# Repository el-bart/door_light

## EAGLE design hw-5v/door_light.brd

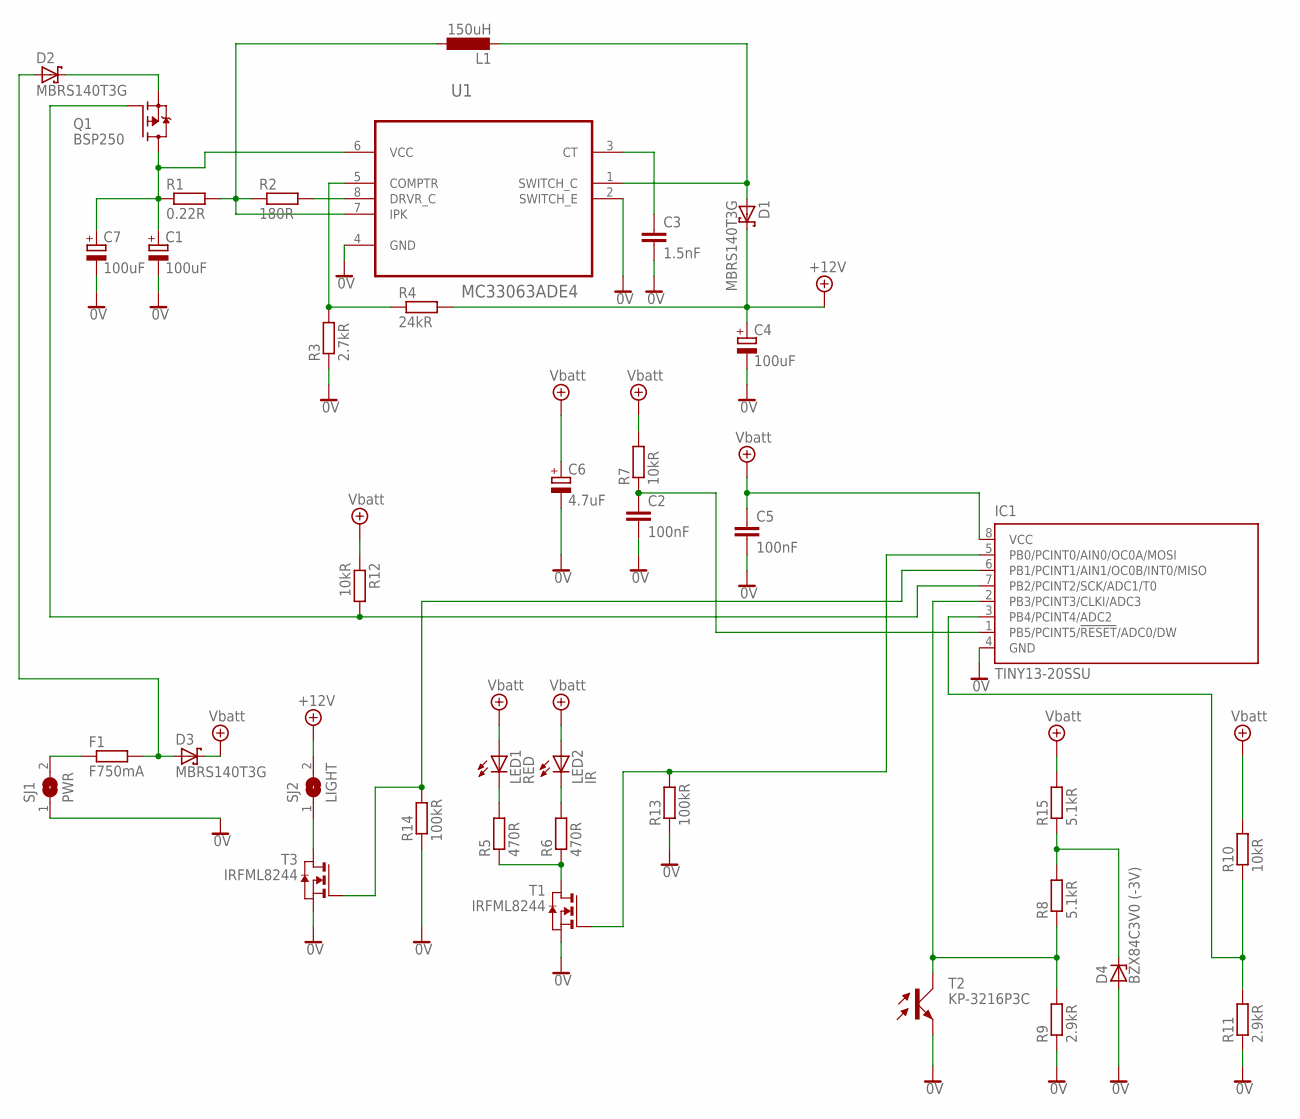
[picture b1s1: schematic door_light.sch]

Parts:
C1, C4, C7: 100uF; 153CLV-0810
C2, C5: 100nF; C1206
C3: 1.5nF; C1206
C6: 4.7uF; 153CLV-0405
D1, D2, D3: MBRS140T3G; SMB
D4: BZX84C3V0 (-3V); TO236
F1: F750mA; MINI_MELF-0207W
IC1: TINY13-20SSU; 8S1
L1: 150uH; PIS2816
LED1: RED; CHIPLED_0603
LED2: IR; CHIPLED_1206
Q1: BSP250; SOT223
R1: 0.22R; M1206
R2: 180R; R0603
R3: 2.7kR; R0603
R4: 24kR; R0603
R5, R6: 470R; R0603
R7, R10, R12: 10kR; R0603
R8, R15: 5.1kR; R0603
R9, R11: 2.9kR; R0603
R13, R14: 100kR; R0603
SJ1: PWR; SJW
SJ2: LIGHT; SJW
T1, T3: IRFML8244; SOT-23
T2: KP-3216P3C; OPTO-TRANS-SIEMENS_BP103
U1: MC33063ADE4; SOIC127P600X175-8N

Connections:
0V: C1.-, C2.2, C3.2, C4.-, C5.2, C6.-, C7.-, D4.A, IC1.4 (GND), R3.1, R9.1, R11.1, R13.1, R14.1, SJ1.1, T1.2 (S), T2.EMITER (E), T3.2 (S), U1.2 (SWITCH_E), U1.4 (GND)
+4.1V: C5.1, C6.+, D3.C, IC1.8 (VCC), LED1.A, LED2.A, R7.2, R10.2, R12.1, R15.2
+12V: C4.+, D1.C, R4.2, SJ2.2
unnamed: LED1.C, R5.2
unnamed: LED2.C, R6.2
unnamed: C1.+, C7.+, Q1.2 (D), Q1.4 (D), R1.1, U1.6 (VCC)
unnamed: R5.1, R6.1, T1.1 (D)
unnamed: D2.C, Q1.3 (S)
unnamed: D4.C, R8.2, R15.1
unnamed: SJ2.1, T3.1 (D)
unnamed: F1.1, SJ1.2
unnamed: C2.1, IC1.1 (PB5/PCINT5/!RESET!/ADC0/DW), R7.1
unnamed: C3.1, U1.3 (CT)
unnamed: D1.A, L1.2, U1.1 (SWITCH_C)
unnamed: IC1.2 (PB3/PCINT3/CLKI/ADC3), R8.1, R9.2, T2.COLLECTOR (C)
unnamed: IC1.7 (PB2/PCINT2/SCK/ADC1/T0), Q1.1 (G), R12.2
unnamed: IC1.5 (PB0/PCINT0/AIN0/OC0A/MOSI), R13.2, T1.3 (G)
unnamed: R2.2, U1.8 (DRVR_C)
unnamed: L1.1, R1.2, R2.1, U1.7 (IPK)
unnamed: IC1.3 (PB4/PCINT4/ADC2), R10.1, R11.2
unnamed: R3.2, R4.1, U1.5 (COMPTR)
unnamed: IC1.6 (PB1/PCINT1/AIN1/OC0B/INT0/MISO), R14.2, T3.3 (G)
unnamed: D2.A, D3.A, F1.2

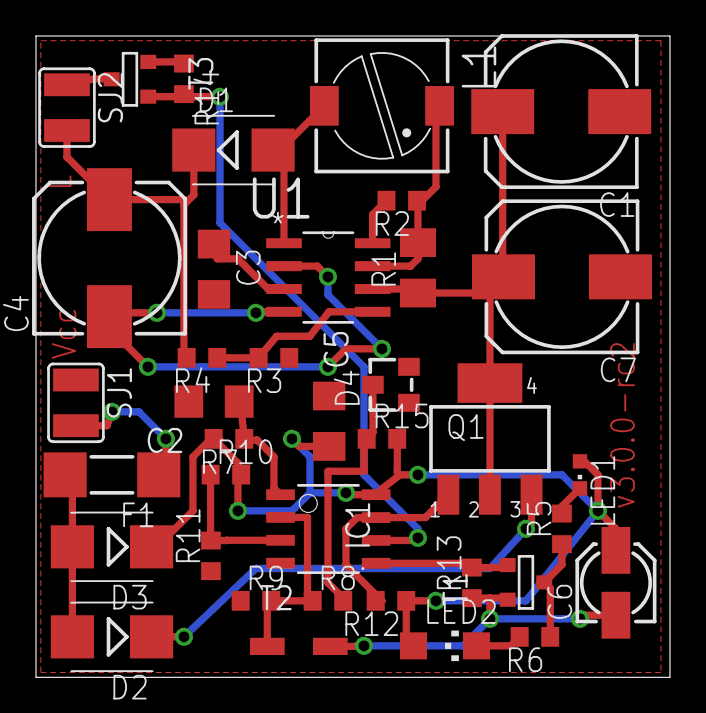
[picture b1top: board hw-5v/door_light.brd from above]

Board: 2 copper layers, 35.2 x 35.6 mm, 38 parts (0 on the bottom side), 23 nets.

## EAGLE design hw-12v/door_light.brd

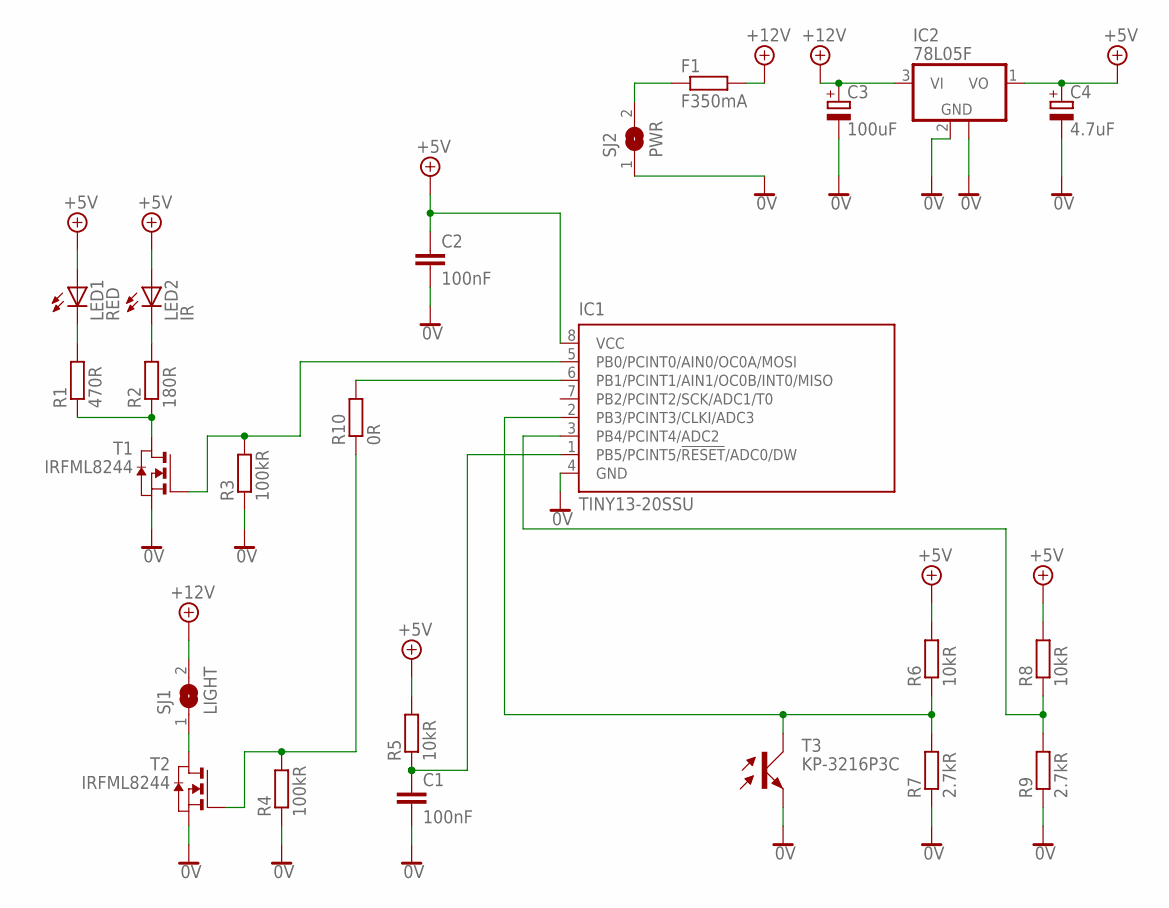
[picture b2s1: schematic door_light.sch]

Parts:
C1, C2: 100nF; C1206
C3: 100uF; 153CLV-0810
C4: 4.7uF; 153CLV-0405
F1: F350mA; MINI_MELF-0204W
IC1: TINY13-20SSU; 8S1
IC2: 78L05F; SOT89
LED1: RED; CHIPLED_0603
LED2: IR; CHIPLED_1206
R1: 470R; R0603
R2: 180R; R0603
R3, R4: 100kR; R0603
R5, R6, R8: 10kR; R0603
R7, R9: 2.7kR; R0603
R10: 0R; R1206W
SJ1: LIGHT; SJW
SJ2: PWR; SJW
T1, T2: IRFML8244; SOT-23
T3: KP-3216P3C; OPTO-TRANS-SIEMENS_BP103

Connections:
0V: C1.2, C2.2, C3.-, C4.-, IC1.4 (GND), IC2.2 (GND), IC2.2@1 (GND), R3.1, R4.1, R7.1, R9.1, SJ2.1, T1.2 (S), T2.2 (S), T3.EMITER (E)
+5V: C2.1, C4.+, IC1.8 (VCC), IC2.1 (VO), LED1.A, LED2.A, R5.2, R6.2, R8.2
+12V: C3.+, F1.2, IC2.3 (VI), SJ1.2
unnamed: LED1.C, R1.2
unnamed: LED2.C, R2.2
unnamed: SJ1.1, T2.1 (D)
unnamed: R1.1, R2.1, T1.1 (D)
unnamed: R4.2, R10.1, T2.3 (G)
unnamed: F1.1, SJ2.2
unnamed: C1.1, IC1.1 (PB5/PCINT5/!RESET!/ADC0/DW), R5.1
unnamed: IC1.2 (PB3/PCINT3/CLKI/ADC3), R6.1, R7.2, T3.COLLECTOR (C)
unnamed: IC1.6 (PB1/PCINT1/AIN1/OC0B/INT0/MISO), R10.2
unnamed: IC1.5 (PB0/PCINT0/AIN0/OC0A/MOSI), R3.2, T1.3 (G)
unnamed: IC1.3 (PB4/PCINT4/ADC2), R8.1, R9.2

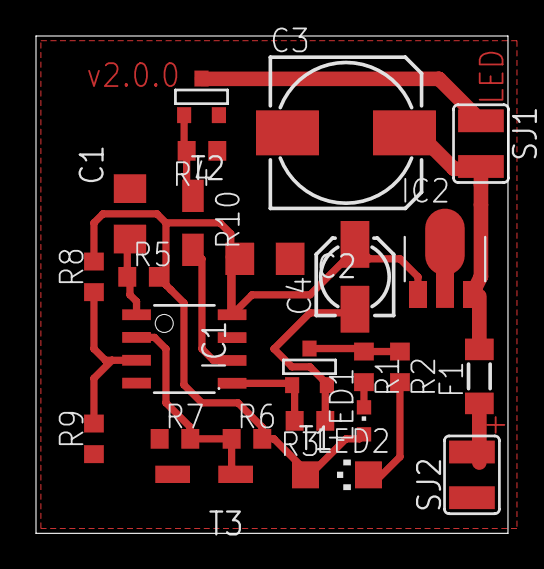
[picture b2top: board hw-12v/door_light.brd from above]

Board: 2 copper layers, 26.2 x 27.6 mm, 24 parts (0 on the bottom side), 14 nets.

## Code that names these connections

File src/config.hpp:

/*
 * config.hpp
 *
 */
#ifndef INCLUDE_CONFIG_HPP_FILE
#define INCLUDE_CONFIG_HPP_FILE

#include <inttypes.h>
#include <avr/io.h>

//
// basic constants
//

// units commonly used
constexpr uint32_t kHz=1000L;
constexpr uint32_t MHz=1000L*kHz;

// clock frequency (9.6MHz with preskaler set to 8)
constexpr uint32_t fcpu = (9*MHz+600*kHz)/8;
// needs to be a define as well...
#define F_CPU fcpu

//
// common types
//
using Millivolts = uint16_t;

//
// misc settings
//

// bits on port definitions
namespace Pin
{
constexpr auto ctrlLed = _BV(PB0);  // control and IR LEDs
constexpr auto light   = _BV(PB1);  // main light
constexpr auto dcDc    = _BV(PB2);  // main light power supply (DC/DC)
constexpr auto irIn    = _BV(PB3);  // IR phototransistor voltage monitoring input
constexpr auto vccIn   = _BV(PB4);  // supply voltage monitoring input
}

// light-related settings
namespace Light
{
constexpr uint8_t irSamples  = 18;      // number of samples to collect per second (each sample is an average of measurements in a corresponding period).
                                        // keep this value, so that PWM's frequency divided by this gives a power of 2 - otherwise code will become big...
constexpr uint8_t irFill     = 50;      // fill level of the PWM for Ctrl setting; 0-255

constexpr uint8_t lightFill  = 0x00;    // PWM fill for main light DC/DC: 0-255

constexpr uint8_t dimIn      =  1;      // number of seconds dim-in should last
constexpr uint8_t lightOn    = 35;      // number of seconds light should remain fully on
constexpr uint8_t dimOut     =  6;      // number of seconds dim-out should last

constexpr uint8_t graceOn    = dimIn+2; // ammount of time where reseting is not possible (avoids blinking)
}

// basic thresholds
namespace Voltage
{
constexpr uint8_t    maxVccThresholdBreach =    3;  // maxumu number of times minimal Vcc threshold can be breached before going down.
constexpr Millivolts minVcc                = 3300;  // minimum operational voltage (3.3[V]);
constexpr Millivolts irThreshold           =   30;  // voltage difference to treat as a trigger (in millivolts)
}

#endif

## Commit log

2013-02-19 datasheets for the components used
2013-02-19 added hardware board
2013-02-21 added version number on board
2013-02-21 added 3rd version number on board
2013-02-22 board overlay limited to actual board's size; minor elements' labels re-ordering
2013-02-26 manual test: application to blink white ledas and control leds
2013-02-26 added compiled elements to the ignore list
2013-02-28 test app to turn everything off
2013-02-28 makefile now is generic
2013-02-28 generic makefile is now used for mtests
2013-02-28 added main build tree
2013-02-28 fuses fixed...
2013-02-28 new build v2.3.1 with protection agains accidental fuses overwrite
2013-02-28 pinout map
2013-02-28 RC frequency is 9.6/8==1.2MHz
2013-02-28 marked ADC number of phototransistor pin
2013-02-28 draft that enables to turn on/off light by approaching hand
2013-02-28 working version (simple though)
2013-02-28 minor cleanup
2013-03-05 TODOs added
2013-06-27 int_t0 test
2013-06-27 ignore files list
2013-06-27 removed leftover from bzr
2013-08-23 TODO on USB added
2013-09-26 TODO moved to devtodo
2013-09-26 more TODOs
2013-11-08 TODO added - new idea on how to make the board
2013-11-09 new idea in english ;)
2013-11-09 documentation update - now PCB is SMD
2013-11-09 TODOs updated
2013-11-09 activeated more layers on pcb view
2013-11-09 pinout updated
2013-11-10 TODO added
2013-11-10 fixed resistor voltage divider
2013-11-10 pads for power and LED connecting are now SMD as well
2013-11-12 coil type changed (bigger one)
2013-11-12 minor alignment update on PCB
2013-11-12 rc-number changed on PCB (not yet labeled though)
2013-11-14 fixed IR led size (was 805, should be 1206)
2013-11-14 replaced fuse with the one of a proper type and size (1812)
2013-11-14 fixed labels on PCB
2013-11-14 blink code update to blink all ports at once (for now)
2013-11-14 infrared elements datasheets added
2013-11-14 fixed invalid path under LED1
2013-11-14 180R size changed from 1206 to 603
2013-11-14 DC/DC converter is nowe powered...
2013-11-14 added missing R to GND from transistors' gates
2013-11-14 minor fixes and first poritng steps forward new software version
2013-11-14 added vim temp failed to ignore list
2013-11-15 Adc moved to separate file + code updated to use new setup
2013-11-15 added dropping 2 least signifficant bits from ADC as a noise
2013-11-15 example application blinking in a way reflecting voltage change
2013-11-15 readme added to state that device needs to be programmed in a slow mode
2013-11-15 removed unused header
2013-11-15 Leds now have separate control classes
2013-11-15 more constants added
2013-11-15 updated 'off' application to new board
2013-11-15 Sampler - class keeping multiple samples of data in a circular buffer
2013-11-15 added power saving mode class
2013-11-15 Pwm is a work in progress
2013-11-15 PWM integration to main has started
2013-11-15 ligh controlling classes are to be reworked
2013-11-15 adding enable/disable and fill() to PWM usage (Led*) - work in progress
2013-11-15 fixed values being set
2013-11-15 default fill for ctrl leds is now in config
2013-11-15 fixed PWM to work as expected, when connected to p-mosfet on output
2013-11-15 removed some garbage from main()
2013-11-15 added method for obtaining PWM's frequency (at compile time)
2013-11-15 replaced on-bard big fuse with the smaller one (the one that has been actually bought)
2013-11-15 Millivolts is now global typedef; draft for the low power handling facility
2013-11-18 created config/Light namespace for light-related settings
2013-11-18 light fill moved to a config
2013-11-18 low power handle has been implemented and is checked once a second
2013-11-18 light triggering work in progress
2013-11-18 added TODOs for 5v version of the hardware
2013-11-18 more TODOs for 12v schematic
2013-11-18 fixed few not-so-bright-namings on the schemas
2013-11-18 added n-mosfet datasheet
2013-11-18 some note on IR elements (after doing measurements)
2013-11-18 IR LED's current note
2013-11-18 added more verbose datasheet on IR diode
2013-11-18 temporary commit
2013-11-18 reverting last commit on main.cpp
2013-11-18 new 12V schema
2013-11-18 added renumerate temp file to git ignores
2013-11-18 recalculated some resitors values
2013-11-19 elements are now more compact
2013-11-19 fixed coliding Vcc and GND on board layout
2013-11-19 fixed R5 size (was 40x should be 603)
2013-11-19 fuse changed from 750mA to 350mA
2013-11-20 TODO added on hardware
2013-11-20 PWM::frequency() now returns more accurate value
2013-11-20 Sampler::average() added
2013-11-20 fixed ADC disabing; removed dropping 2lsbs of ADC result as a noise - nosise is being averaged elsewhere
2013-11-20 working version of light on/off, w/o dim-in/out
2013-11-20 fixed PWM for channel B which is now n-mosfet as well (inverted polarity is NOT required)
2013-11-20 fixed light led control + both led derive privately from implementation
2013-11-20 Sampler has now fill() and size() methods
2013-11-20 main now works fine with real power leds turned on as well
2013-11-20 dim handler draft
2013-11-20 dimming works fine - needs to be integrated with IR readings though
2013-11-20 working version w/o Sampler - just simple 'prev' value, updated during start() and once a second
2013-11-20 minimum Vcc is now 3.3[V] (3x1.1 == 3x low-power eneloops)
2013-11-20 low power handler has been reworked to have check and halt() calls separate, to allow user's code to be added, before halting
2013-11-20 added low power handing code to main()
2013-11-20 minor style and comment fixed + constants improvements
2013-11-20 class for watchdog handling
2013-11-20 watchdog added to main code
2013-11-20 most TODOs marked as done (or removed)
2013-11-20 TODO added on fluorecesnce light
2013-11-20 fixed issue with fluoroluminescence light by adding average values of measurements
2013-11-20 changed board name to v2.0.0 on 12V version
2013-12-04 added DC/DC on/off support in software
2013-12-04 12V version schema is ready, TODOs fixed; PCB is draft-done - to be tested and improved
2013-12-05 route fixes; changed fuse to bigger package (1A)
2013-12-09 added FIR filter model (octave file)
2013-12-09 temporary octave files are added to ignore list
2013-12-12 fixed invalid 10kR resistor size
2013-12-12 fixed invalid p-mosfet control
2013-12-12 comments fixes; added constant for grace on-time
2013-12-12 added todo o missing resistor
2013-12-12 grace period when starting added
2013-12-12 size of the binary decreased thanks to dividing by the power of 2
2013-12-12 comment on irSamples added
2013-12-12 TODO added on IR measuring for 5V version
2013-12-13 removed unneeded todo
2013-12-13 fixed BSP250's pull-down to be a pull-up (10kR)
2013-12-13 added -3V zenner for ensuring reasonable measurements of IR light change
2016-03-09 TODOs for version 4 added
2017-12-28 TODO list moved to a markdown file + added TODO on NFC-based configuraion
2017-12-28 removed extra whitespaces
